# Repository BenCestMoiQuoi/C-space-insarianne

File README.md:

# C-space-insarianne

Dossier de notre première année C'space
Pour le compte de l'association INS'aéro
Sur le projet C'space.

Utilisation d'une librairy personalisée 
https://github.com/BenCestMoiQuoi/INSARIANNE

Pour le reste, tout est dedans

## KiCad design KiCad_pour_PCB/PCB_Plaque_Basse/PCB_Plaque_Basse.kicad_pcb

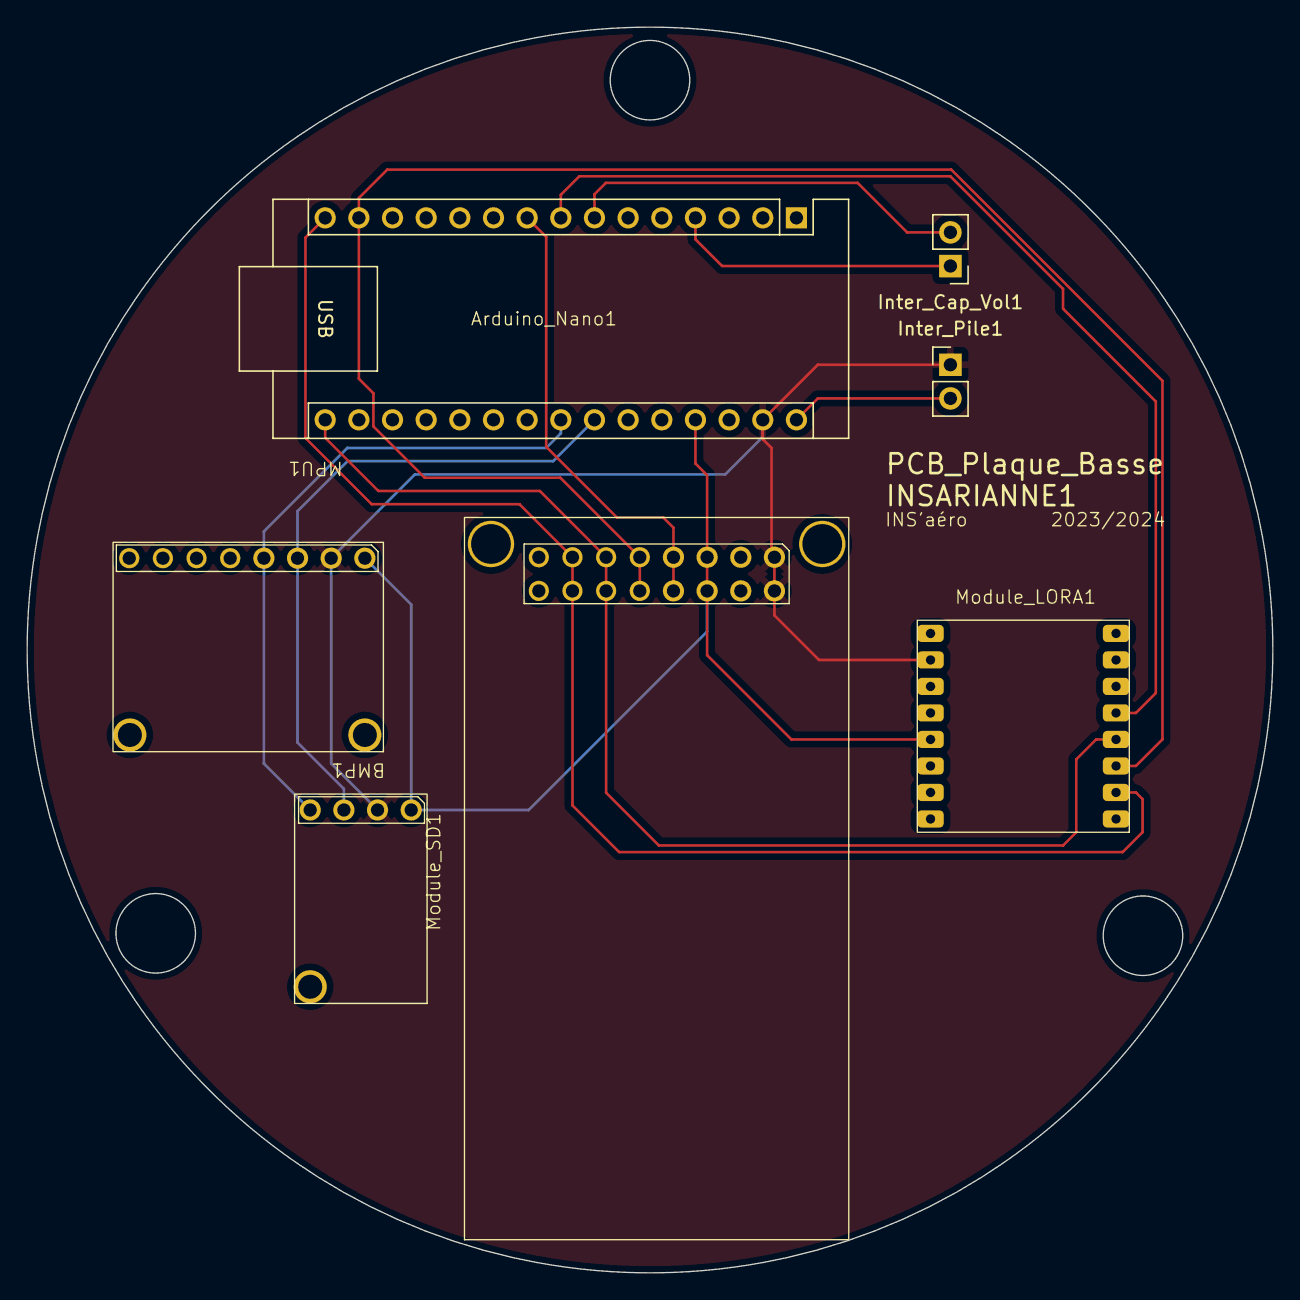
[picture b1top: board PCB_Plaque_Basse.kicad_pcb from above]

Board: 2 copper layers, 94.0 x 94.0 mm, 7 parts (0 on the bottom side), 12 nets.

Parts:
Arduino_Nano1: Arduino_Nano
BMP1: BMP180
Inter_Cap_Vol1: PinHeader_1x02_P2.54mm_Vertical
Inter_Pile1: PinHeader_1x02_P2.54mm_Vertical
MPU1: MPU6050
Module_LORA1: Module_LORA
Module_SD1: Module_SD

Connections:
unnamed: Arduino_Nano1.27 (5V), BMP1.1 (VCC), MPU1.1 (VCC), Module_LORA1.4 (VDD), Module_SD1.3 (5V)
unnamed: Arduino_Nano1.23 (A4), BMP1.4 (SDA), MPU1.4 (SDA)
unnamed: Arduino_Nano1.24 (A5), BMP1.3 (SCL), MPU1.3 (SCL)
unnamed: Arduino_Nano1.7 (D4), Inter_Cap_Vol1.2 (Cap)
unnamed: Arduino_Nano1.8 (D5), Module_LORA1.13 (NSS)
unnamed: Arduino_Nano1.9 (D6), Module_SD1.4 (CS)
unnamed: Arduino_Nano1.14 (D11), Module_LORA1.11 (MOSI), Module_SD1.5 (MOSI)
unnamed: Arduino_Nano1.15 (D12), Module_LORA1.10 (MISO), Module_SD1.7 (MISO)
unnamed: Arduino_Nano1.16 (D13), Module_LORA1.12 (SCK), Module_SD1.6 (SCK)
unnamed: Arduino_Nano1.30 (Vin), Inter_Pile1.2 (Vin)
unnamed: Arduino_Nano1.29 (GND), BMP1.2 (GND), Inter_Pile1.1 (GND), MPU1.2 (GND), Module_LORA1.7 (GND), Module_SD1.1 (GND)
unnamed: Arduino_Nano1.4 (GND), Inter_Cap_Vol1.1 (GND)

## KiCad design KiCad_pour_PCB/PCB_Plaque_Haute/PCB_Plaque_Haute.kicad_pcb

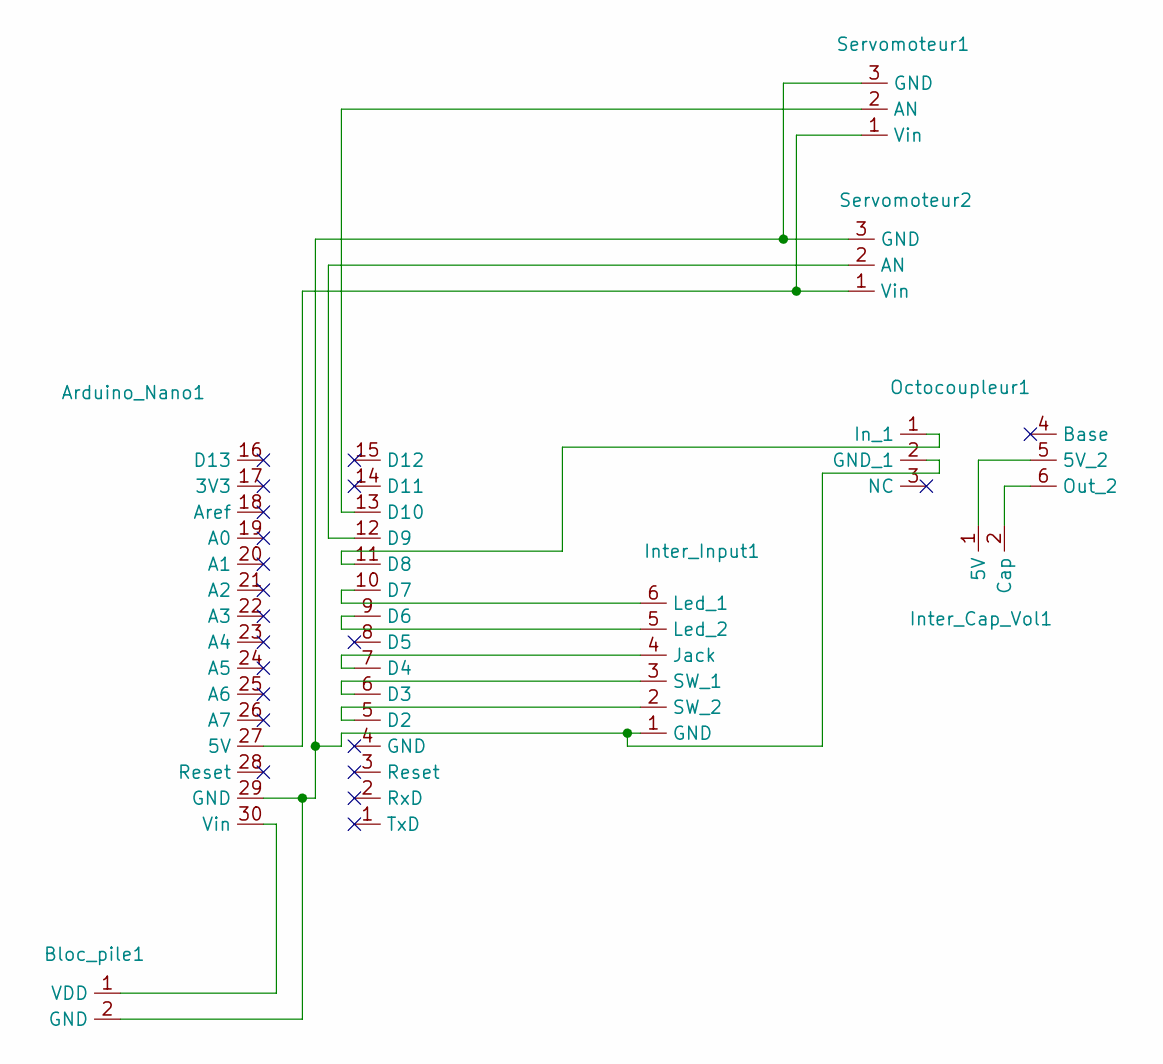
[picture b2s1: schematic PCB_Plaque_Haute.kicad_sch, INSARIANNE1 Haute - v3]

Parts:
Arduino_Nano1: Arduino_Nano
Bloc_pile1: PinHeader_1x02_P2.54mm_Vertical
Inter_Cap_Vol1: PinHeader_1x02_P2.54mm_Vertical
Inter_Input1: PinHeader_1x06_P2.54mm_Vertical
Octocoupleur1: Octocoupleur
Servomoteur1, Servomoteur2: PinHeader_1x03_P2.54mm_Vertical

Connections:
unnamed: Arduino_Nano1.27 (5V), Servomoteur1.1 (Vin), Servomoteur2.1 (Vin)
unnamed: Arduino_Nano1.5 (D2), Inter_Input1.2 (SW_2)
unnamed: Arduino_Nano1.6 (D3), Inter_Input1.3 (SW_1)
unnamed: Arduino_Nano1.7 (D4), Inter_Input1.4 (Jack)
unnamed: Arduino_Nano1.9 (D6), Inter_Input1.5 (Led_2)
unnamed: Arduino_Nano1.10 (D7), Inter_Input1.6 (Led_1)
unnamed: Arduino_Nano1.11 (D8), Octocoupleur1.1 (In_1)
unnamed: Arduino_Nano1.12 (D9), Servomoteur2.2 (AN)
unnamed: Arduino_Nano1.13 (D10), Servomoteur1.2 (AN)
unnamed: Arduino_Nano1.30 (Vin), Bloc_pile1.1 (VDD)
unnamed: Arduino_Nano1.29 (GND), Bloc_pile1.2 (GND), Inter_Input1.1 (GND), Octocoupleur1.2 (GND_1), Servomoteur1.3 (GND), Servomoteur2.3 (GND)
unnamed: Inter_Cap_Vol1.1 (5V), Octocoupleur1.5 (5V_2)
unnamed: Inter_Cap_Vol1.2 (Cap), Octocoupleur1.6 (Out_2)

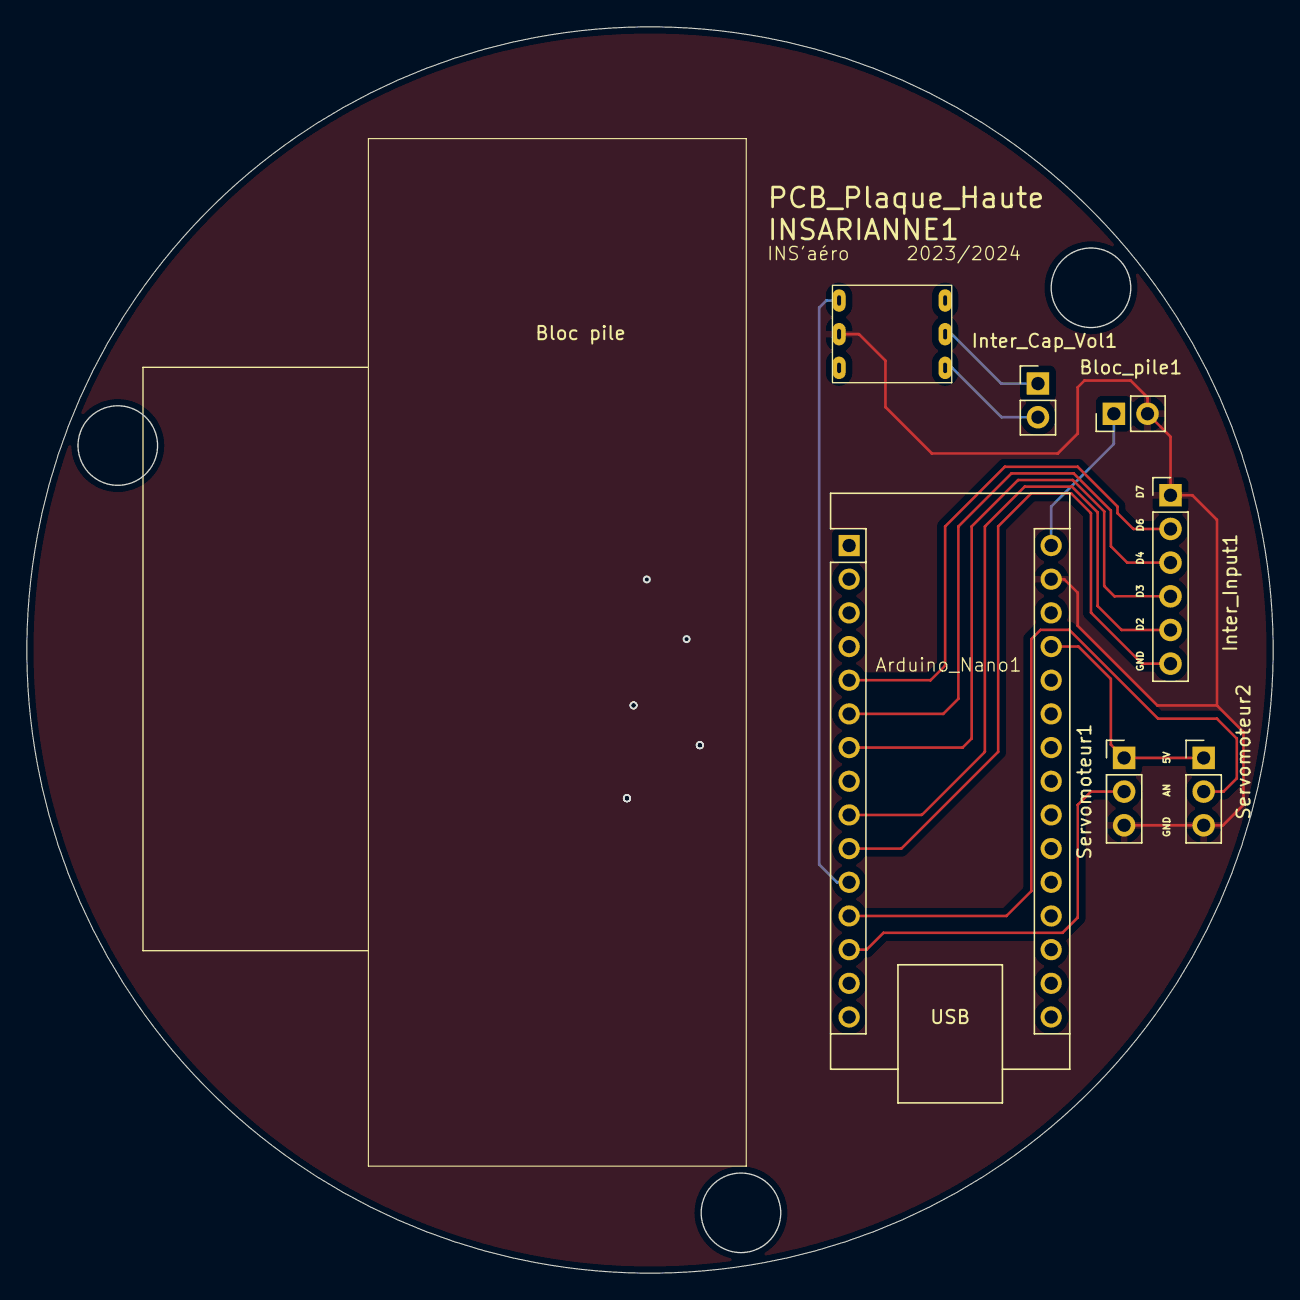
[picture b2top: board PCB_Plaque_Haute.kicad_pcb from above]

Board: 2 copper layers, 94.0 x 93.9 mm, 7 parts (0 on the bottom side), 13 nets.

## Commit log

2024-01-20 Add solidworks files
2024-01-20 Add programme files
2024-01-24 Chengement LED sur support
2024-01-24 Petit ajustement
2024-01-25 Add main_sans-SD
2024-01-25 Add Main_sans-SD-Servo and Main_sans-Servo
2024-01-25 Add Main_sans-Servo
2024-01-25 Correct some mistakes
2024-01-30 Add test_lib
2024-01-30 test.ino
2024-01-30 Add test2
2024-02-08 Add SD_sol.ino
2024-02-18 new changes
2024-03-13 premier test
2024-03-14 Programme assez approximatif non testé comprenant l'envoi des données par le module LoRa
2024-03-31 Envoi des données par le LoRa
2024-04-02 Version finale ultime
2024-04-02 C'est reparti
2024-04-03 Ajout code interface graphique -> PyQt6
2024-04-04 Et voilà le changement effectué! Hésite pas si il faut que je change autre chose
2024-04-11 premiers codes pour la communication entre deux cartes
2024-04-12 PCB et Schema_Electonique Création de la V1 de la PCB et du schéma Electronique En attante des dimensions de chaque composants
2024-04-12 Deleted backup and add .gitignore
2024-04-14 Premiers essais de com serie
2024-05-10 Avancement v2/v3
2024-05-10 Ajustement SD
2024-05-10 Update SD.ino
    Ajout de quelques paramètres
2024-05-10 Delete SD/sd.ino
    Erreur d'ajout de fichier
2024-05-10 Update SD.ino
    changement de la valeur writing par défaut (elle était à 0 au lieu de 1)
2024-05-17 Avancement carte PCB
2024-05-23 Update experience.ino
    commentaires
2024-06-07 PCB_Fin
2024-06-07 Petits_changements
2024-06-10 Nouvelle version PCB _ Suite RCE3
2024-06-18 Update Autonome.ino
    ajout de l'optocoupleur
2024-06-18 Update Embarque.ino
    ajout de l'optocoupleur
2024-06-19 modification des noms des dossiers pour clarifier le stockage
2024-06-19 modif noms dossiers
2024-06-19 modification des noms des dossiers
2024-06-19 code test de l'optocoupleur
2024-06-19 correction oubli point virgule
2024-06-19 ajout des instructions pour le test de l'opto
2024-06-19 modification du mode d'ouverture de l'opto côté capteur
2024-07-07 Fin carte PCB
2024-07-07 Création du folder "final" avec les 3 parties
2024-07-07 Néttoyage Dossier PCB
2024-07-07 Modifs de l'embarqué et sol
2024-07-07 MAJ Autonome.ino Pour dernière vérif
2024-07-07 Changements mineurs
2024-07-07 Embarque
2024-07-07 Optocoupleur dans la verif sol
2024-07-07 Optocoipleur et verif sol
2024-07-07 correct one mistake
2024-07-07 modified Sol and Add Python programs
2024-07-07 petits changements
2024-07-08 Changement d'axes
2024-07-08 Gros taff sur les programmes finaux
2024-07-11 Last Push of 2024 ON EST QUALIFIE !!!!!!!!!!!!!!!!!!!!!!!!!!!!!!!!!!!!!!!!!!!!!!!!!!!!!!!!!!!!!!!!!!!!!!!!!!!!!!!!!!!!!!!!!!!!!!!!!!!!!!!!!!!!!!!!!!!!!!!!!!!!!!!!!!!!!!!!!!!!!!
2024-08-13 Tri de fin d'année Tri sur le dossier en prévision d'une utilisation pour l'année prochaine Prise en compte de la modification de la librairie utilisée
2024-08-22 Correction trous de perçage PCB Truc stupide d'un triangle équilatérales Plus besoin de faire des trous manuellement
